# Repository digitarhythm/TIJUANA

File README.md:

# TIJUANA
TReK G50 TIJUANA KiCAD Project

[Firmware repository](https://github.com/digitarhythm/qmk_firmware/tree/digitarhythm/keyboards/trek/tijuana)

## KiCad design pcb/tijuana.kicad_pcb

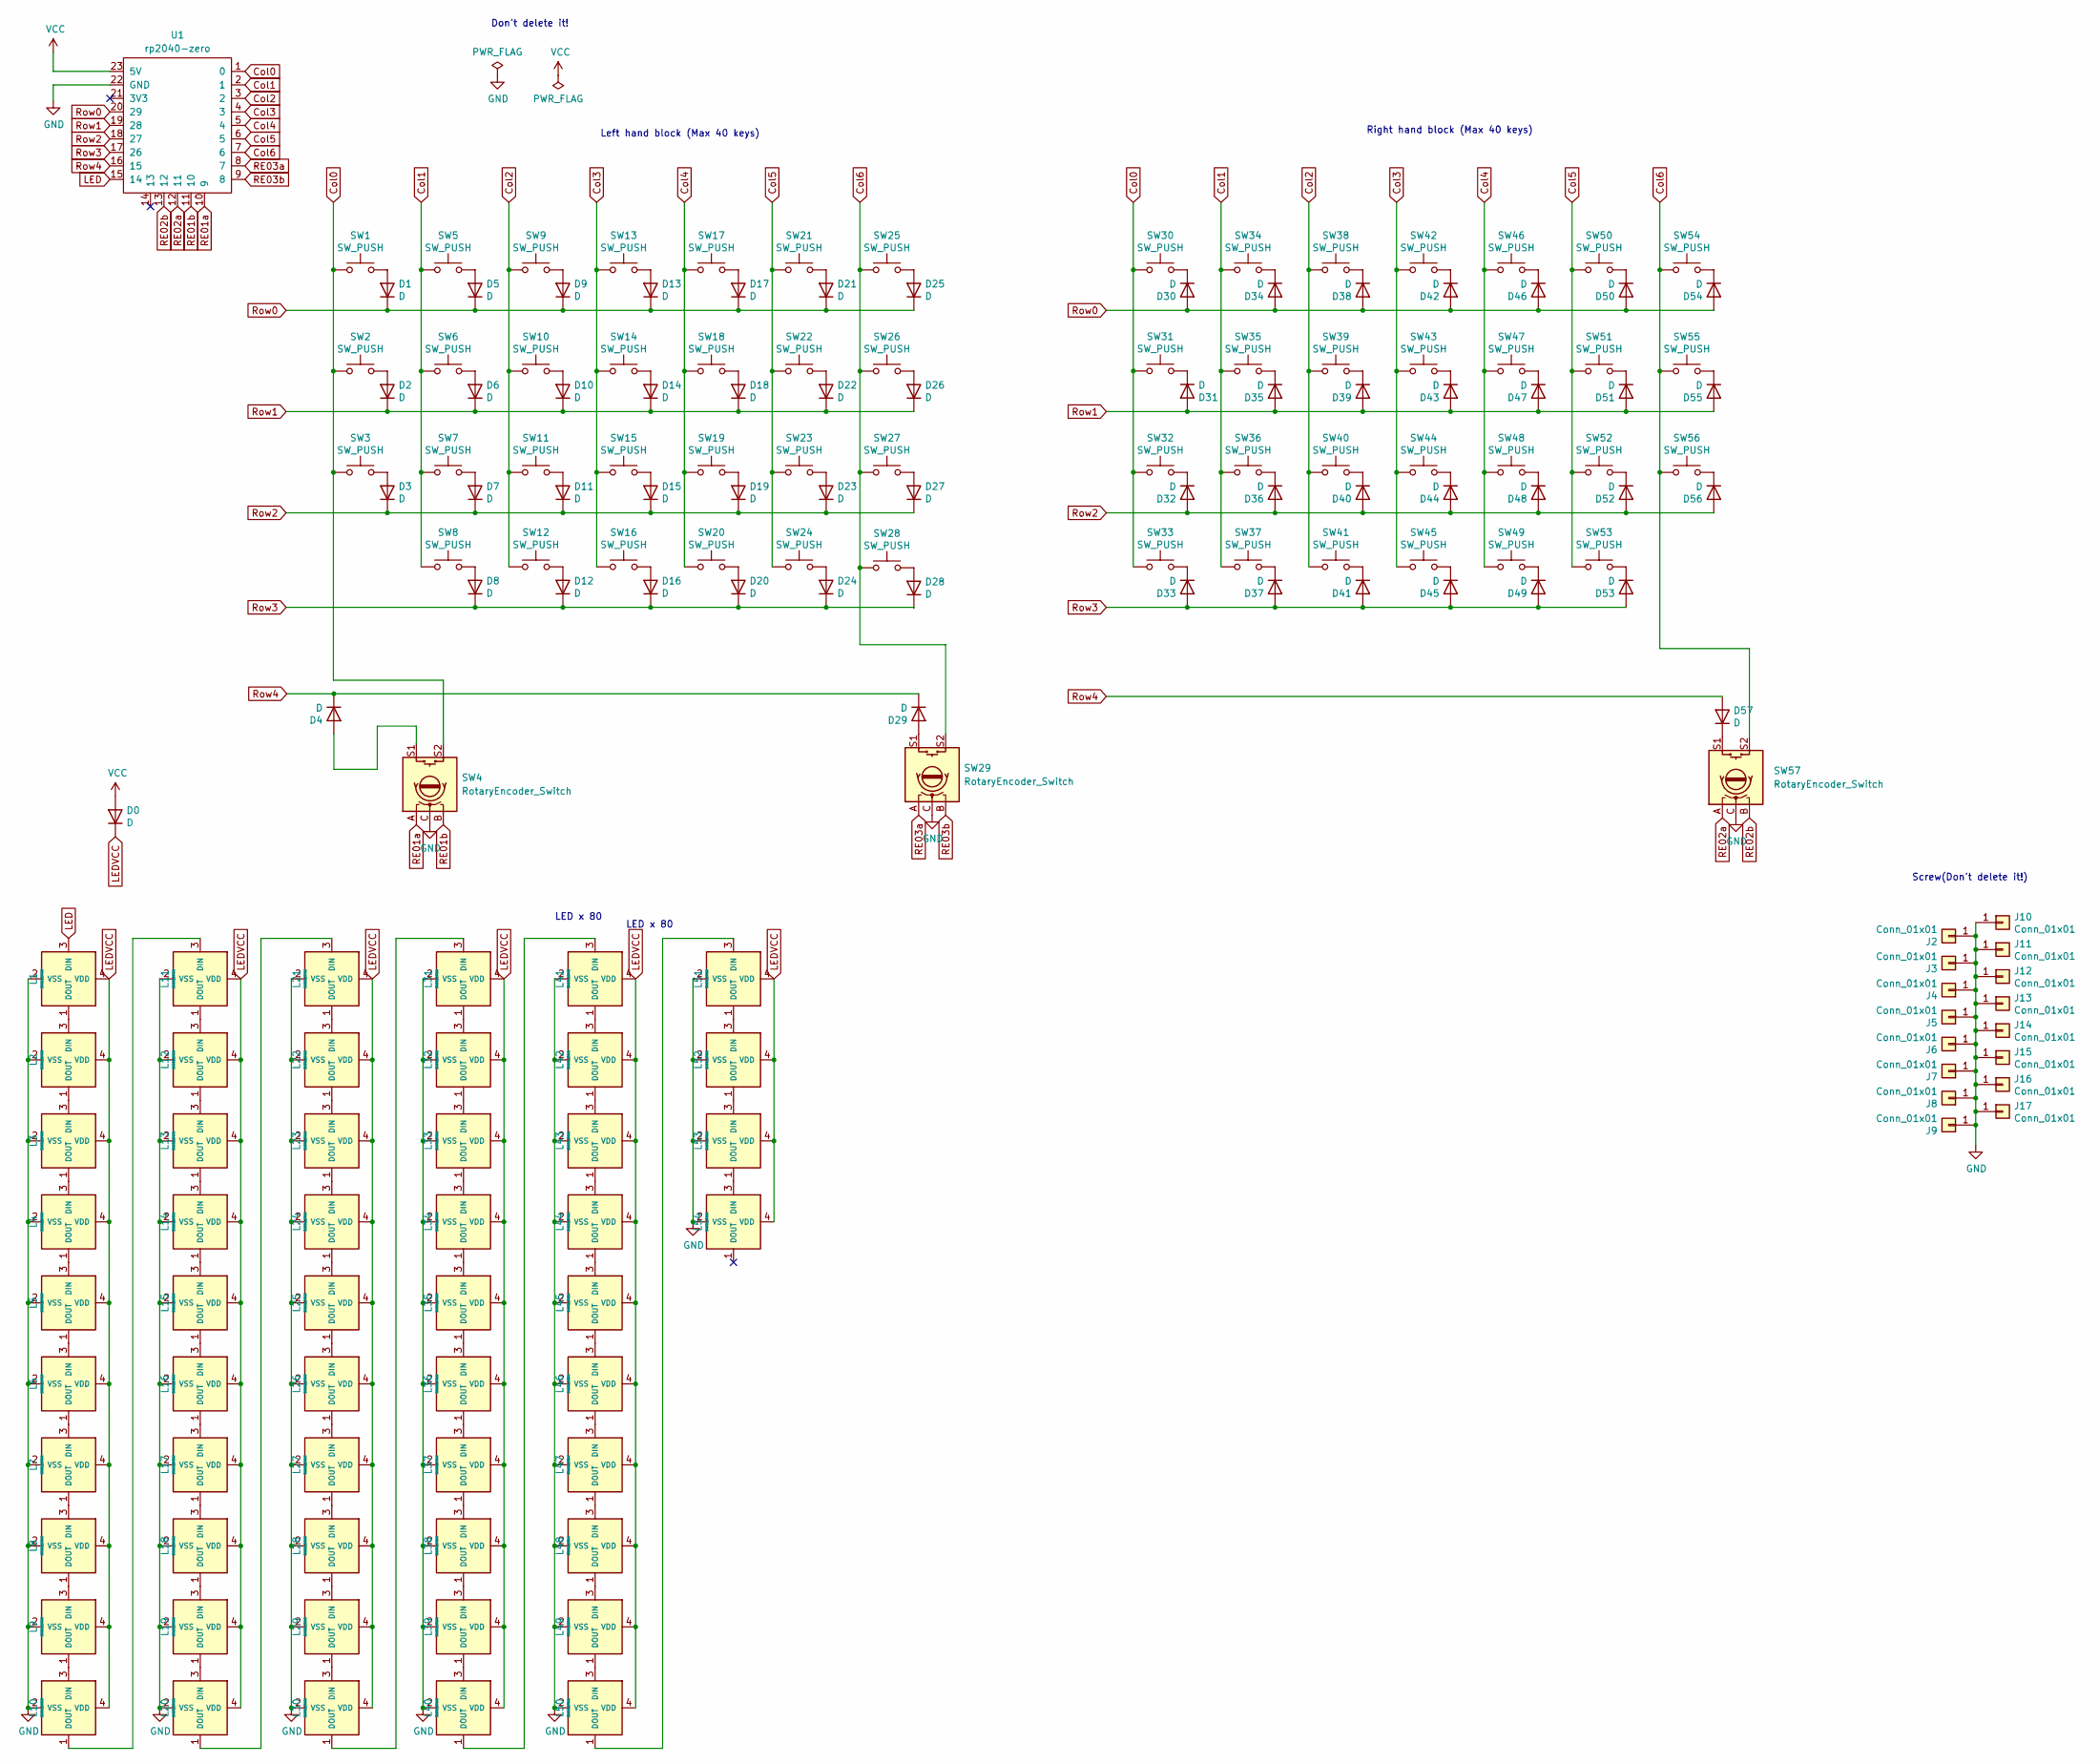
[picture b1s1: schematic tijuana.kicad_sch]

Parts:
D0, D1, D2, D3, D4, D5, D6, D7, D8, D9, D10, D11, D12, D13, D14, D15, D16, D17, D18, D19, D20, D21, D22, D23, D24, D25, D26, D27, D28, D29, D30, D31, D32, D33, D34, D35, D36, D37, D38, D39, D40, D41, D42, D43, D44, D45, D46, D47, D48, D49, D50, D51, D52, D53, D54, D55, D56, D57: D; Diode_SMD
J2, J3, J4, J5, J6, J7: Conn_01x01; m2_Screw_Hole_EdgeCuts
J8, J9, J10, J11, J12, J13, J14, J15, J16, J17: Conn_01x01; m2_Screw_Hole_Fab
L1, L2, L3, L4, L5, L6, L7, L8, L9, L10, L11, L12, L13, L14, L15, L16, L17, L18, L19, L20, L21, L22, L23, L24, L25, L26, L27, L28, L29, L30, L31, L32, L33, L34, L35, L36, L37, L38, L39, L40, L41, L42, L43, L44, L45, L46, L47, L48, L49, L50, L51, L52, L53, L54: SK6812MINI; LED_SK6812MINI-E_BL
SW1, SW5, SW6, SW7, SW9, SW10, SW11, SW13, SW14, SW15, SW17, SW18, SW19, SW20, SW21, SW22, SW23, SW24, SW25, SW26, SW27, SW28, SW30, SW31, SW32, SW33, SW34, SW35, SW36, SW38, SW39, SW40, SW42, SW43, SW44, SW46, SW47, SW48, SW49, SW50, SW51, SW52, SW53, SW55: SW_PUSH; CherryMX_Hotswap_1u
SW2, SW8, SW16, SW37, SW45, SW54: SW_PUSH; CherryMX_Hotswap_1.25u
SW3, SW56: SW_PUSH; CherryMX_Hotswap_1.5u
SW4, SW29, SW57: RotaryEncoder_Switch; SW_Cherry_MX_1.00u_Kailh_EC12
SW12, SW41: SW_PUSH; CherryMX_Hotswap_1.75u
U1: rp2040-zero; rp2040-zero-smd-rev-with-th

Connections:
Col0: SW1.1, SW2.1, SW3.1, SW4.S2, SW30.1, SW31.1, SW32.1, SW33.1, U1.1 (0)
Col1: SW5.1, SW6.1, SW7.1, SW8.1, SW34.1, SW35.1, SW36.1, SW37.1, U1.2 (1)
Col2: SW9.1, SW10.1, SW11.1, SW12.1, SW38.1, SW39.1, SW40.1, SW41.1, U1.3 (2)
Col3: SW13.1, SW14.1, SW15.1, SW16.1, SW42.1, SW43.1, SW44.1, SW45.1, U1.4 (3)
Col4: SW17.1, SW18.1, SW19.1, SW20.1, SW46.1, SW47.1, SW48.1, SW49.1, U1.5 (4)
Col5: SW21.1, SW22.1, SW23.1, SW24.1, SW50.1, SW51.1, SW52.1, SW53.1, U1.6 (5)
Col6: SW25.1, SW26.1, SW27.1, SW28.1, SW29.S2, SW54.1, SW55.1, SW56.1, SW57.S2, U1.7 (6)
GND: J2.1, J3.1, J4.1, J5.1, J6.1, J7.1, J8.1, J9.1, J10.1, J11.1, J12.1, J13.1, J14.1, J15.1, J16.1, J17.1, L1.2 (VSS), L2.2 (VSS), L3.2 (VSS), L4.2 (VSS), L5.2 (VSS), L6.2 (VSS), L7.2 (VSS), L8.2 (VSS), L9.2 (VSS), L10.2 (VSS), L11.2 (VSS), L12.2 (VSS), L13.2 (VSS), L14.2 (VSS), L15.2 (VSS), L16.2 (VSS), L17.2 (VSS), L18.2 (VSS), L19.2 (VSS), L20.2 (VSS), L21.2 (VSS), L22.2 (VSS), L23.2 (VSS), L24.2 (VSS), L25.2 (VSS), L26.2 (VSS), L27.2 (VSS), L28.2 (VSS), L29.2 (VSS), L30.2 (VSS), L31.2 (VSS), L32.2 (VSS), L33.2 (VSS), L34.2 (VSS), L35.2 (VSS), L36.2 (VSS), L37.2 (VSS), L38.2 (VSS), L39.2 (VSS), L40.2 (VSS), L41.2 (VSS), L42.2 (VSS), L43.2 (VSS), L44.2 (VSS), L45.2 (VSS), L46.2 (VSS), L47.2 (VSS), L48.2 (VSS), L49.2 (VSS), L50.2 (VSS), L51.2 (VSS), L52.2 (VSS), L53.2 (VSS), L54.2 (VSS), SW4.C, SW29.C, SW57.C, U1.22 (GND)
LED: L1.3 (DIN), U1.15 (14)
LEDVCC: D0.1 (K), L1.4 (VDD), L2.4 (VDD), L3.4 (VDD), L4.4 (VDD), L5.4 (VDD), L6.4 (VDD), L7.4 (VDD), L8.4 (VDD), L9.4 (VDD), L10.4 (VDD), L11.4 (VDD), L12.4 (VDD), L13.4 (VDD), L14.4 (VDD), L15.4 (VDD), L16.4 (VDD), L17.4 (VDD), L18.4 (VDD), L19.4 (VDD), L20.4 (VDD), L21.4 (VDD), L22.4 (VDD), L23.4 (VDD), L24.4 (VDD), L25.4 (VDD), L26.4 (VDD), L27.4 (VDD), L28.4 (VDD), L29.4 (VDD), L30.4 (VDD), L31.4 (VDD), L32.4 (VDD), L33.4 (VDD), L34.4 (VDD), L35.4 (VDD), L36.4 (VDD), L37.4 (VDD), L38.4 (VDD), L39.4 (VDD), L40.4 (VDD), L41.4 (VDD), L42.4 (VDD), L43.4 (VDD), L44.4 (VDD), L45.4 (VDD), L46.4 (VDD), L47.4 (VDD), L48.4 (VDD), L49.4 (VDD), L50.4 (VDD), L51.4 (VDD), L52.4 (VDD), L53.4 (VDD), L54.4 (VDD)
unnamed: D1.2 (A), SW1.2
unnamed: D2.2 (A), SW2.2
unnamed: D3.2 (A), SW3.2
unnamed: D4.2 (A), SW4.S1
unnamed: D5.2 (A), SW5.2
unnamed: D6.2 (A), SW6.2
unnamed: D7.2 (A), SW7.2
unnamed: D8.2 (A), SW8.2
unnamed: D9.2 (A), SW9.2
unnamed: D10.2 (A), SW10.2
unnamed: D11.2 (A), SW11.2
unnamed: D12.2 (A), SW12.2
unnamed: D13.2 (A), SW13.2
unnamed: D14.2 (A), SW14.2
unnamed: D15.2 (A), SW15.2
unnamed: D16.2 (A), SW16.2
unnamed: D17.2 (A), SW17.2
unnamed: D18.2 (A), SW18.2
unnamed: D19.2 (A), SW19.2
unnamed: D20.2 (A), SW20.2
unnamed: D21.2 (A), SW21.2
unnamed: D22.2 (A), SW22.2
unnamed: D23.2 (A), SW23.2
unnamed: D24.2 (A), SW24.2
unnamed: D25.2 (A), SW25.2
unnamed: D26.2 (A), SW26.2
unnamed: D27.2 (A), SW27.2
unnamed: D28.2 (A), SW28.2
unnamed: D29.2 (A), SW29.S1
unnamed: D30.1 (K), SW30.2
unnamed: D31.1 (K), SW31.2
unnamed: D32.1 (K), SW32.2
unnamed: D33.1 (K), SW33.2
unnamed: D34.1 (K), SW34.2
unnamed: D35.1 (K), SW35.2
unnamed: D36.1 (K), SW36.2
unnamed: D37.1 (K), SW37.2
unnamed: D38.1 (K), SW38.2
unnamed: D39.1 (K), SW39.2
unnamed: D40.1 (K), SW40.2
unnamed: D41.1 (K), SW41.2
unnamed: D42.1 (K), SW42.2
unnamed: D43.1 (K), SW43.2
unnamed: D44.1 (K), SW44.2
unnamed: D45.1 (K), SW45.2
unnamed: D46.1 (K), SW46.2
unnamed: D47.1 (K), SW47.2
unnamed: D48.1 (K), SW48.2
unnamed: D49.1 (K), SW49.2
unnamed: D50.1 (K), SW50.2
unnamed: D51.1 (K), SW51.2
unnamed: D52.1 (K), SW52.2
unnamed: D53.1 (K), SW53.2
unnamed: D54.1 (K), SW54.2
unnamed: D55.1 (K), SW55.2
unnamed: D56.1 (K), SW56.2
unnamed: D57.1 (K), SW57.S1
unnamed: L1.1 (DOUT), L2.3 (DIN)
unnamed: L2.1 (DOUT), L3.3 (DIN)
unnamed: L3.1 (DOUT), L4.3 (DIN)
unnamed: L4.1 (DOUT), L5.3 (DIN)
unnamed: L5.1 (DOUT), L6.3 (DIN)
unnamed: L6.1 (DOUT), L7.3 (DIN)
unnamed: L7.1 (DOUT), L8.3 (DIN)
unnamed: L8.1 (DOUT), L9.3 (DIN)
unnamed: L9.1 (DOUT), L10.3 (DIN)
unnamed: L10.1 (DOUT), L11.3 (DIN)
unnamed: L11.1 (DOUT), L12.3 (DIN)
unnamed: L12.1 (DOUT), L13.3 (DIN)
unnamed: L13.1 (DOUT), L14.3 (DIN)
unnamed: L14.1 (DOUT), L15.3 (DIN)
unnamed: L15.1 (DOUT), L16.3 (DIN)
unnamed: L16.1 (DOUT), L17.3 (DIN)
unnamed: L17.1 (DOUT), L18.3 (DIN)
unnamed: L18.1 (DOUT), L19.3 (DIN)
unnamed: L19.1 (DOUT), L20.3 (DIN)
unnamed: L20.1 (DOUT), L21.3 (DIN)
unnamed: L21.1 (DOUT), L22.3 (DIN)
unnamed: L22.1 (DOUT), L23.3 (DIN)
unnamed: L23.1 (DOUT), L24.3 (DIN)
unnamed: L24.1 (DOUT), L25.3 (DIN)
unnamed: L25.1 (DOUT), L26.3 (DIN)
unnamed: L26.1 (DOUT), L27.3 (DIN)
unnamed: L27.1 (DOUT), L28.3 (DIN)
unnamed: L28.1 (DOUT), L29.3 (DIN)
unnamed: L29.1 (DOUT), L30.3 (DIN)
unnamed: L30.1 (DOUT), L31.3 (DIN)
unnamed: L31.1 (DOUT), L32.3 (DIN)
unnamed: L32.1 (DOUT), L33.3 (DIN)
unnamed: L33.1 (DOUT), L34.3 (DIN)
unnamed: L34.1 (DOUT), L35.3 (DIN)
unnamed: L35.1 (DOUT), L36.3 (DIN)
unnamed: L36.1 (DOUT), L37.3 (DIN)
unnamed: L37.1 (DOUT), L38.3 (DIN)
unnamed: L38.1 (DOUT), L39.3 (DIN)
unnamed: L39.1 (DOUT), L40.3 (DIN)
unnamed: L40.1 (DOUT), L41.3 (DIN)
unnamed: L41.1 (DOUT), L42.3 (DIN)
unnamed: L42.1 (DOUT), L43.3 (DIN)
unnamed: L43.1 (DOUT), L44.3 (DIN)
unnamed: L44.1 (DOUT), L45.3 (DIN)
unnamed: L45.1 (DOUT), L46.3 (DIN)
unnamed: L46.1 (DOUT), L47.3 (DIN)
unnamed: L47.1 (DOUT), L48.3 (DIN)
unnamed: L48.1 (DOUT), L49.3 (DIN)
unnamed: L49.1 (DOUT), L50.3 (DIN)
unnamed: L50.1 (DOUT), L51.3 (DIN)
unnamed: L51.1 (DOUT), L52.3 (DIN)
unnamed: L52.1 (DOUT), L53.3 (DIN)
unnamed: L53.1 (DOUT), L54.3 (DIN)
RE01a: SW4.A, U1.10 (9)
RE01b: SW4.B, U1.11 (10)
RE02a: SW57.A, U1.12 (11)
RE02b: SW57.B, U1.13 (12)
RE03a: SW29.A, U1.8 (7)
RE03b: SW29.B, U1.9 (8)
Row0: D1.1 (K), D5.1 (K), D9.1 (K), D13.1 (K), D17.1 (K), D21.1 (K), D25.1 (K), D30.2 (A), D34.2 (A), D38.2 (A), D42.2 (A), D46.2 (A), D50.2 (A), D54.2 (A), U1.20 (29)
Row1: D2.1 (K), D6.1 (K), D10.1 (K), D14.1 (K), D18.1 (K), D22.1 (K), D26.1 (K), D31.2 (A), D35.2 (A), D39.2 (A), D43.2 (A), D47.2 (A), D51.2 (A), D55.2 (A), U1.19 (28)
Row2: D3.1 (K), D7.1 (K), D11.1 (K), D15.1 (K), D19.1 (K), D23.1 (K), D27.1 (K), D32.2 (A), D36.2 (A), D40.2 (A), D44.2 (A), D48.2 (A), D52.2 (A), D56.2 (A), U1.18 (27)
Row3: D8.1 (K), D12.1 (K), D16.1 (K), D20.1 (K), D24.1 (K), D28.1 (K), D33.2 (A), D37.2 (A), D41.2 (A), D45.2 (A), D49.2 (A), D53.2 (A), U1.17 (26)
Row4: D4.1 (K), D29.1 (K), D57.2 (A), U1.16 (15)
VCC: D0.2 (A), U1.23 (5V)

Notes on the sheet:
LED x 80
Left hand block (Max 40 keys)
Screw(Don't delete it!)
Don't delete it!
Right hand block (Max 40 keys)

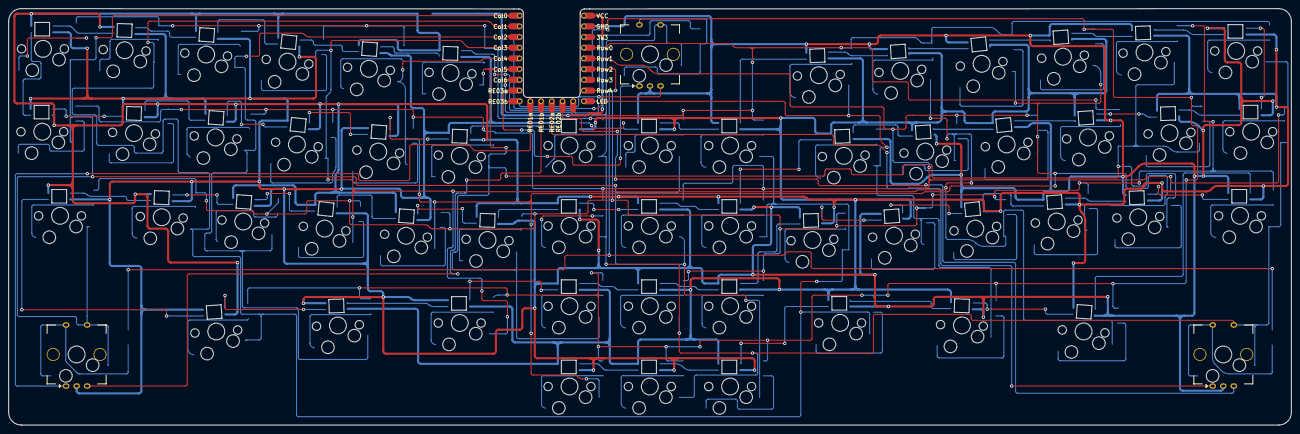
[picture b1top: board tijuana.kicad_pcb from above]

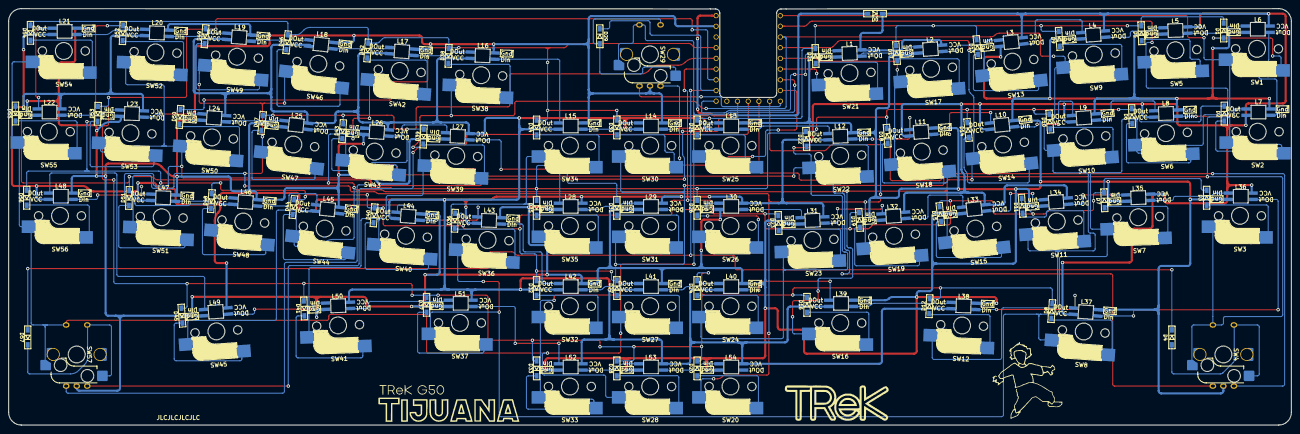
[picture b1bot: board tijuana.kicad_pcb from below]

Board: 2 copper layers, 304.4 x 98.8 mm, 172 parts (2 on the bottom side), 132 nets.

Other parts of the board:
G000, G001: LOGO

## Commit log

2024-04-06 update LICENCE
